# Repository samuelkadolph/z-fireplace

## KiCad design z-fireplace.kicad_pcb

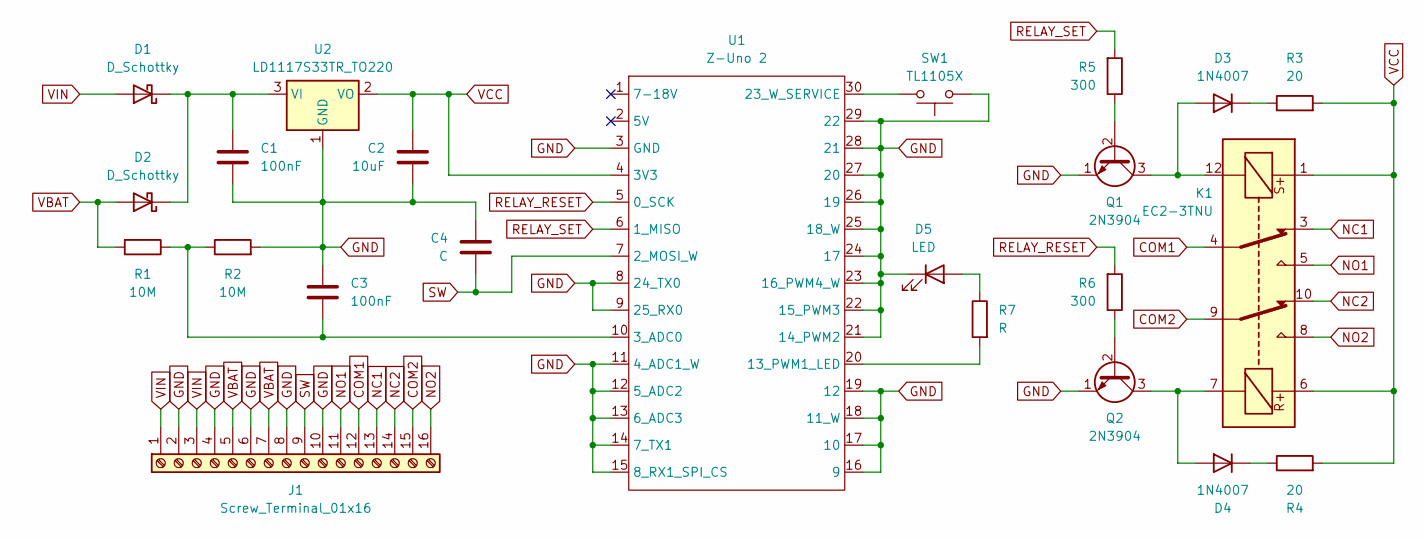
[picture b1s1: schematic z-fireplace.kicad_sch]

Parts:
C1, C3: 100nF; C_Disc_D5.0mm_W2.5mm_P5.00mm
C2: 10uF; C_Disc_D5.0mm_W2.5mm_P5.00mm
C4: C
D1, D2: D_Schottky; D_DO-41_SOD81_P10.16mm_Horizontal
D3, D4: 1N4007; D_DO-41_SOD81_P10.16mm_Horizontal
D5: LED; PinHeader_1x02_P2.54mm_Vertical
J1: Screw_Terminal_01x16; Phoenix 1844785
K1: EC2-3TNU; Relay_DPDT_Kemet_EC2_DoubleCoil
Q1, Q2: 2N3904; TO-92_Inline
R1, R2: 10M; R_Axial_DIN0204_L3.6mm_D1.6mm_P5.08mm_Horizontal
R3, R4: 20; R_Axial_DIN0204_L3.6mm_D1.6mm_P5.08mm_Horizontal
R5, R6: 300; R_Axial_DIN0204_L3.6mm_D1.6mm_P5.08mm_Horizontal
R7: R; R_Axial_DIN0204_L3.6mm_D1.6mm_P5.08mm_Horizontal
SW1: TL1105X
U1: Z-Uno 2; DIP-30_W17.78mm
U2: LD1117S33TR_TO220; TO-220-3_Horizontal_TabDown

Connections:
COM1: J1.12, K1.4
COM2: J1.15, K1.9
NC1: J1.13, K1.3
NC2: J1.14, K1.10
NO1: J1.11, K1.5
NO2: J1.16, K1.8
unnamed: C1.1, D1.1 (K), D2.1 (K), U2.3 (VI)
unnamed: D3.2 (A), K1.12, Q1.3 (C)
unnamed: D3.1 (K), R3.1
unnamed: D4.2 (A), K1.7, Q2.3 (C)
unnamed: D4.1 (K), R4.1
unnamed: D5.2 (A), R7.1
unnamed: Q1.2 (B), R5.1
unnamed: Q2.2 (B), R6.1
unnamed: C3.2, R1.1, R2.1, U1.10 (3_ADC0)
unnamed: R7.2, U1.20 (13_PWM1_LED)
unnamed: SW1.2, U1.30 (23_W_SERVICE)
RELAY_RESET: R6.2, U1.5 (0_SCK)
RELAY_SET: R5.2, U1.6 (1_MISO)
SW: C4.2, J1.9, U1.7 (2_MOSI_W)
VBAT: D2.2 (A), J1.5, J1.7, R1.2
VCC: C2.1, K1.1, K1.6, R3.2, R4.2, U1.4 (3V3), U2.2 (VO)
VIN: D1.2 (A), J1.1, J1.3

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
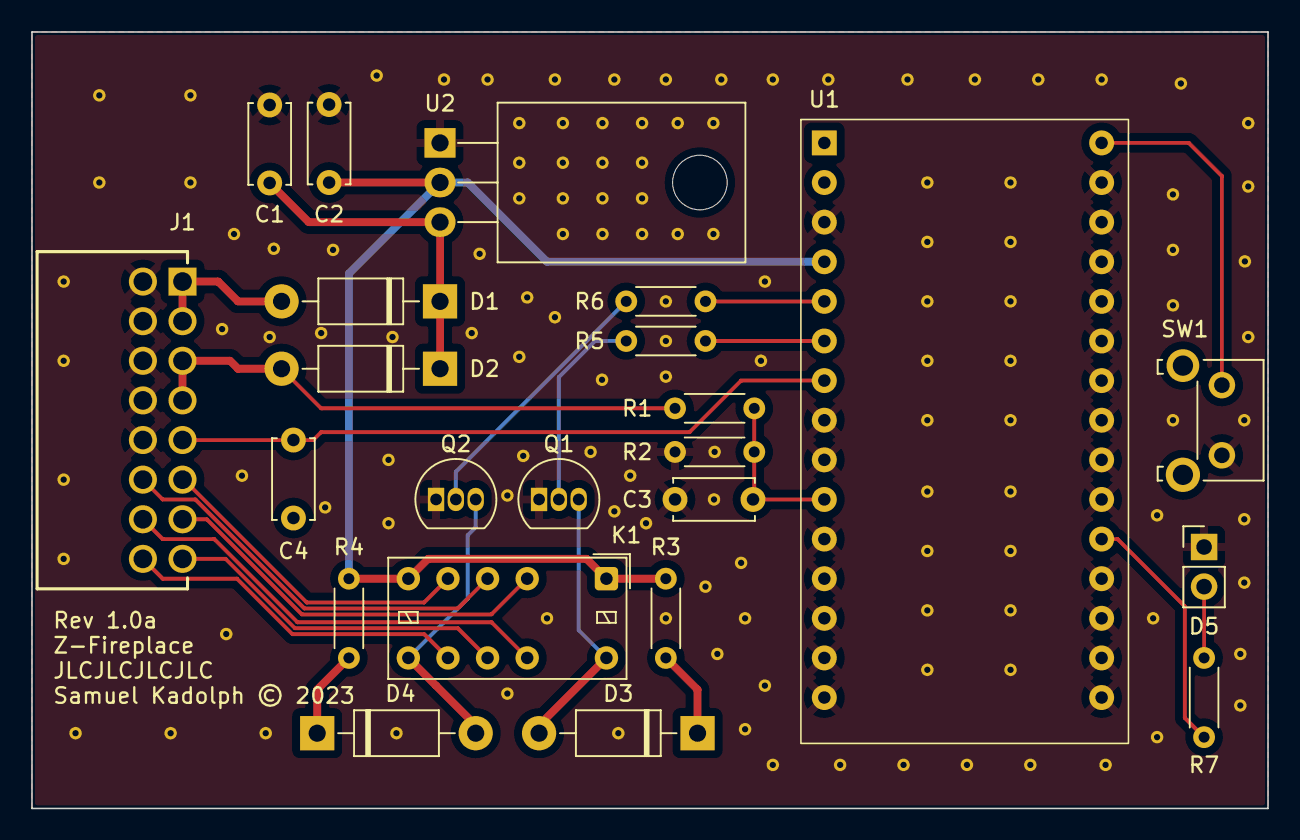
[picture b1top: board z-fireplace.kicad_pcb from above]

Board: 2 copper layers, 79.2 x 49.8 mm, 23 parts (0 on the bottom side), 24 nets.

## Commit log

2023-11-17 Add kicad project

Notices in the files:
z-fireplace.kicad_pcb:
Samuel Kadolph © 2023
